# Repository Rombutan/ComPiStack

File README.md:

# YOU MUST SET A KICAD VARIABLE CALLED 'BASE_GIT_FOLDER' to the location of the root, git folder you cloned.

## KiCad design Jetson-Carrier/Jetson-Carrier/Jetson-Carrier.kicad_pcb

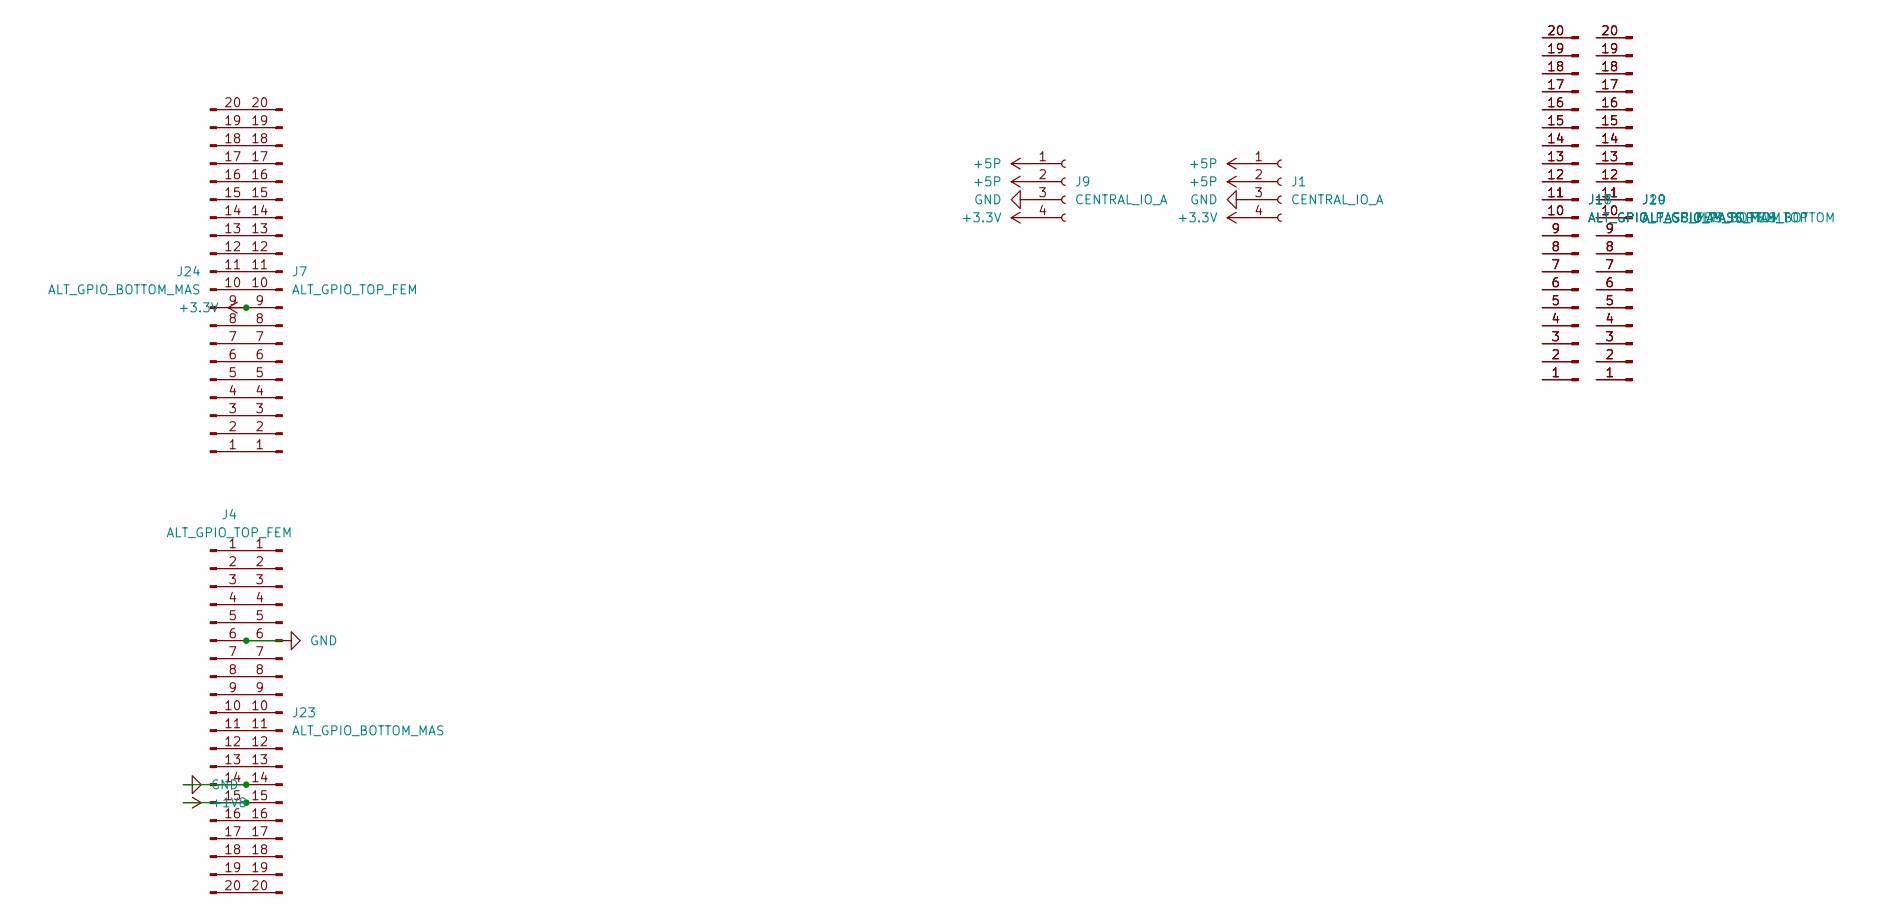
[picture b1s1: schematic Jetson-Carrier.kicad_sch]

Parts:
J1, J9: CENTRAL_IO_A; PinHeader_1x04_P2.54mm_Vertical
J4, J7: ALT_GPIO_TOP_FEM; 10132797-021100LF
J16, J20: ALT_GPIO_PASS_FEM_TOP; 10132797-021100LF
J17, J19: ALT_GPIO_PASS_MAS_BOTTOM; 10132798-022100LF
J23, J24: ALT_GPIO_BOTTOM_MAS; 10132798-022100LF

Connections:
+1V8: J4.15, J23.15
+3V3: J1.4, J7.9, J9.4, J24.9
+5P: J1.1, J1.2, J9.1, J9.2
GND: J1.3, J4.6, J4.14, J9.3, J23.6, J23.14
unnamed: J7.1, J24.1
unnamed: J7.2, J24.2
unnamed: J7.3, J24.3
unnamed: J16.1, J17.1
unnamed: J16.2, J17.2
unnamed: J16.3, J17.3
unnamed: J16.4, J17.4
unnamed: J16.5, J17.5
unnamed: J16.6, J17.6
unnamed: J16.7, J17.7
unnamed: J16.8, J17.8
unnamed: J16.9, J17.9
unnamed: J16.10, J17.10
unnamed: J16.11, J17.11
unnamed: J16.12, J17.12
unnamed: J16.13, J17.13
unnamed: J16.14, J17.14
unnamed: J16.15, J17.15
unnamed: J16.16, J17.16
unnamed: J16.17, J17.17
unnamed: J16.18, J17.18
unnamed: J16.19, J17.19
unnamed: J16.20, J17.20
unnamed: J19.1, J20.1
unnamed: J19.2, J20.2
unnamed: J19.3, J20.3
unnamed: J19.4, J20.4
unnamed: J19.5, J20.5
unnamed: J19.6, J20.6
unnamed: J19.7, J20.7
unnamed: J19.8, J20.8
unnamed: J19.9, J20.9
unnamed: J19.10, J20.10
unnamed: J19.11, J20.11
unnamed: J19.12, J20.12
unnamed: J19.13, J20.13
unnamed: J19.14, J20.14
unnamed: J19.15, J20.15
unnamed: J19.16, J20.16
unnamed: J19.17, J20.17
unnamed: J19.18, J20.18
unnamed: J19.19, J20.19
unnamed: J19.20, J20.20
unnamed: J4.1, J23.1
unnamed: J4.2, J23.2
unnamed: J4.3, J23.3
unnamed: J4.4, J23.4
unnamed: J4.5, J23.5
unnamed: J4.7, J23.7
unnamed: J4.8, J23.8
unnamed: J4.9, J23.9
unnamed: J4.10, J23.10
unnamed: J4.11, J23.11
unnamed: J4.12, J23.12
unnamed: J4.13, J23.13
unnamed: J4.16, J23.16
unnamed: J4.17, J23.17
unnamed: J4.18, J23.18
unnamed: J4.19, J23.19
unnamed: J4.20, J23.20
unnamed: J7.4, J24.4
unnamed: J7.5, J24.5
unnamed: J7.6, J24.6
unnamed: J7.7, J24.7
unnamed: J7.8, J24.8
unnamed: J7.10, J24.10
unnamed: J7.11, J24.11
unnamed: J7.12, J24.12
unnamed: J7.13, J24.13
unnamed: J7.14, J24.14
unnamed: J7.15, J24.15
unnamed: J7.16, J24.16
unnamed: J7.17, J24.17
unnamed: J7.18, J24.18
unnamed: J7.19, J24.19
unnamed: J7.20, J24.20

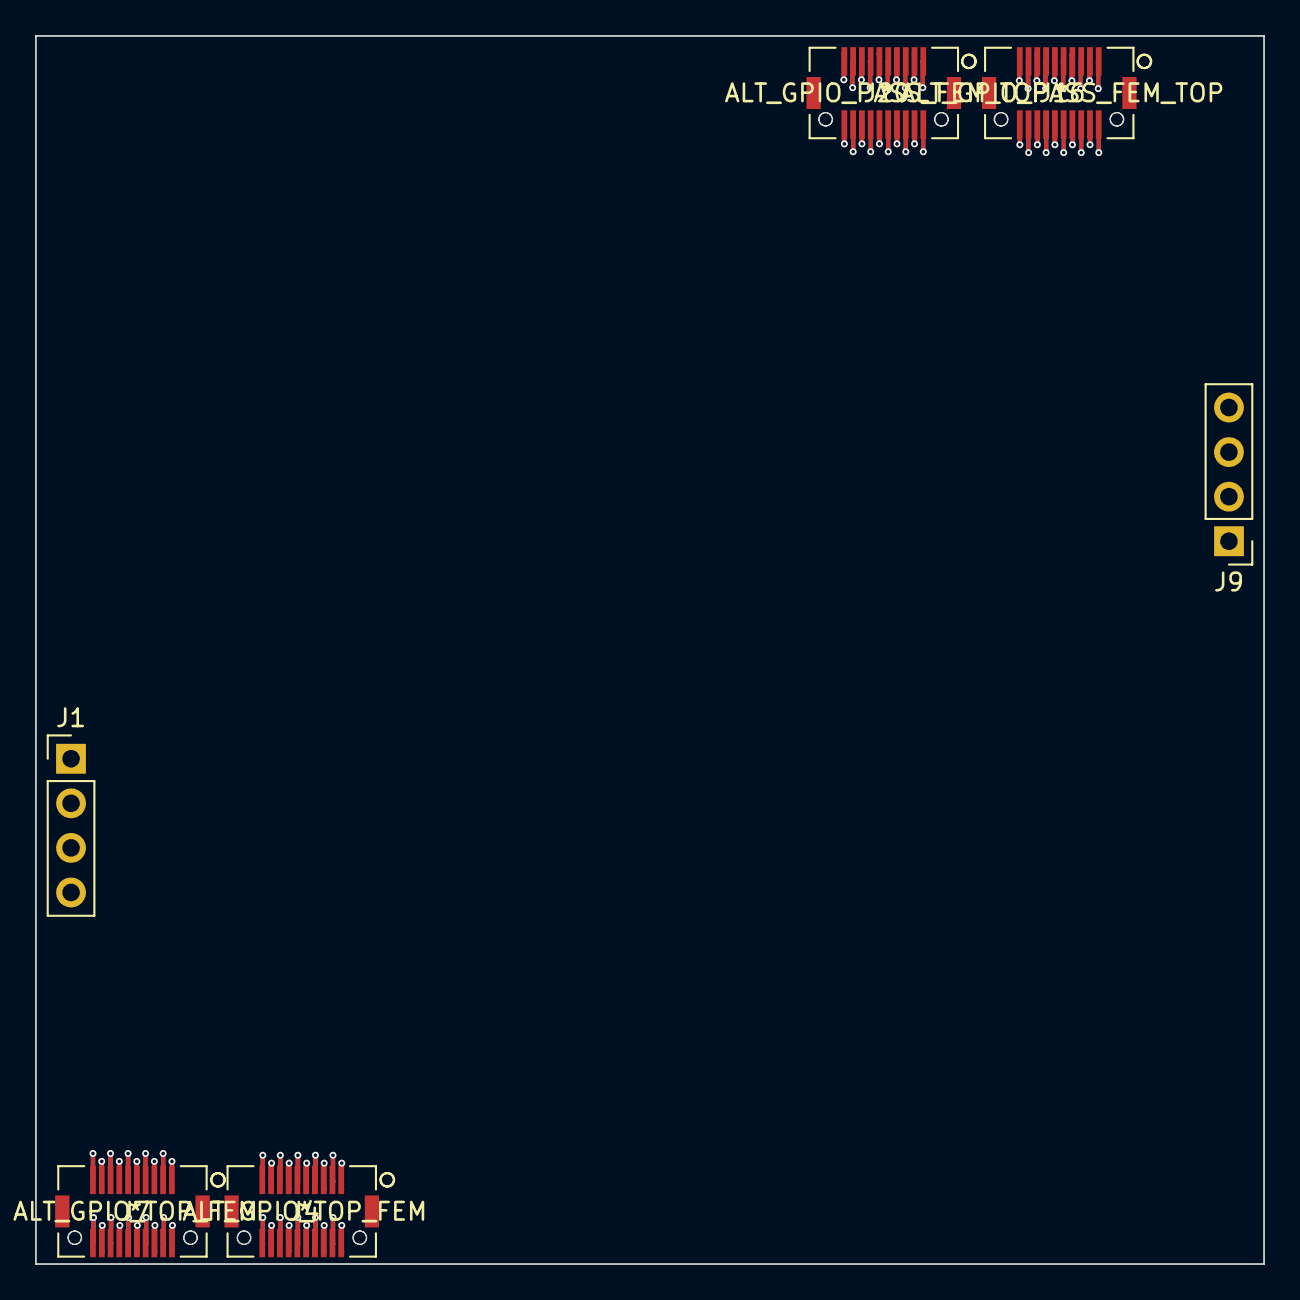
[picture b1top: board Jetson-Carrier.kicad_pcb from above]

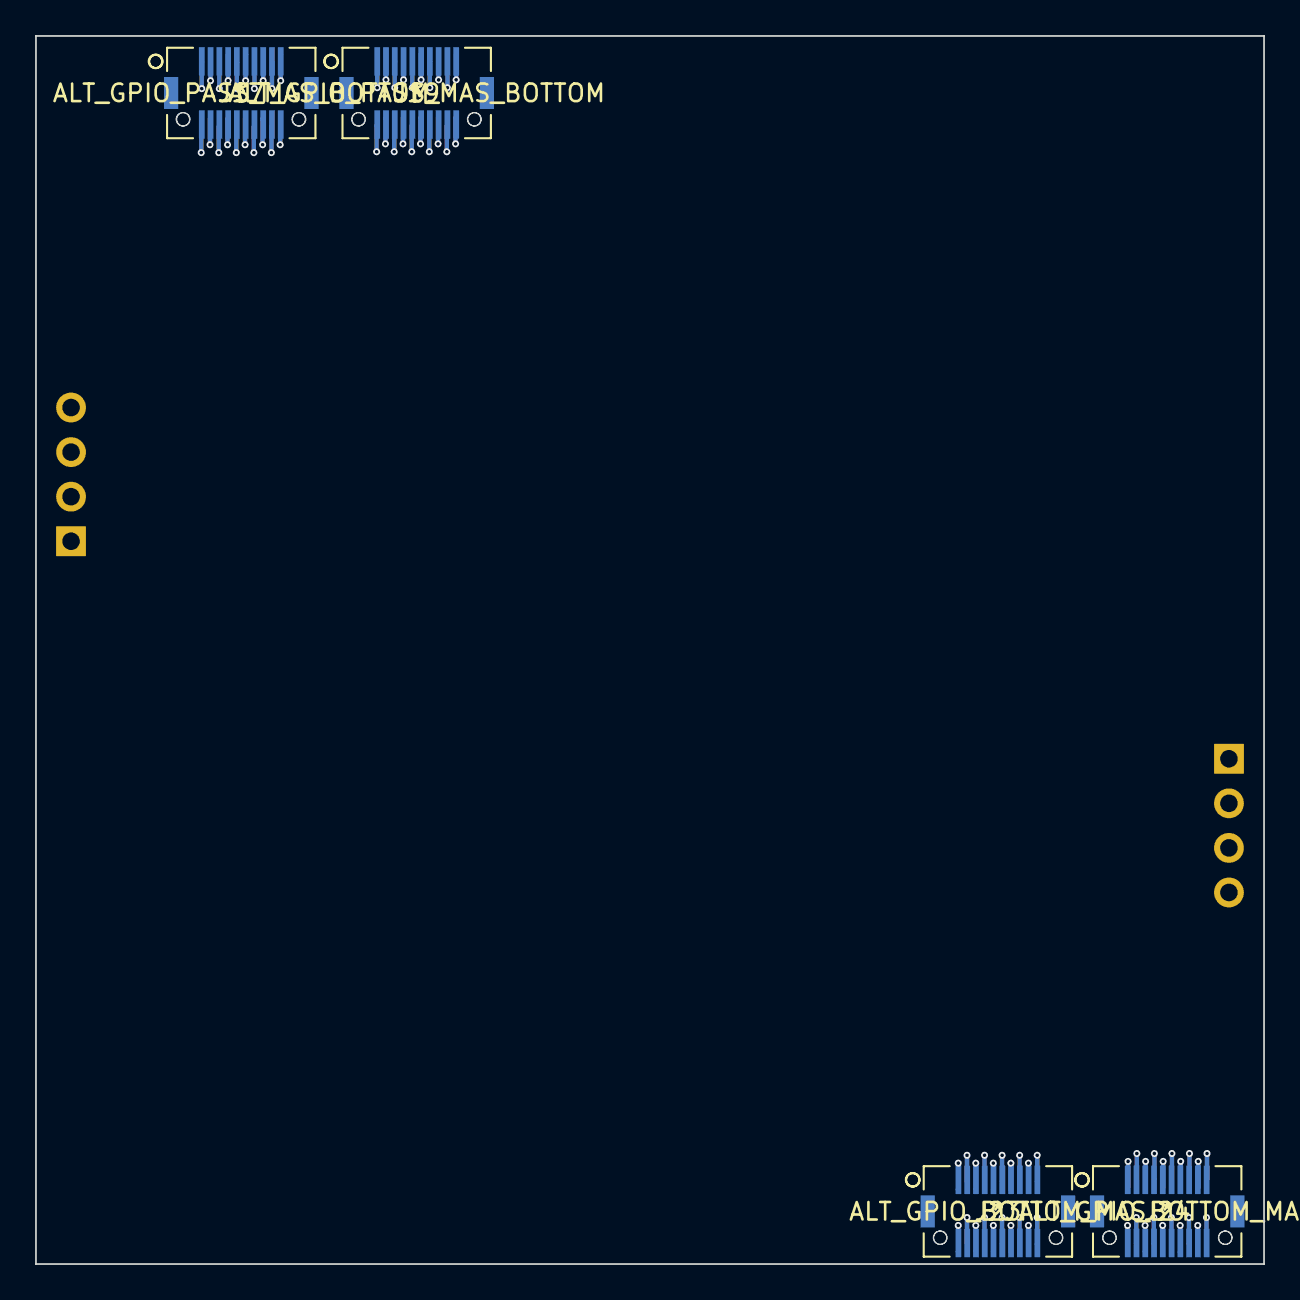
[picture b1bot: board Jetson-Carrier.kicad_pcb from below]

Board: 2 copper layers, 70.0 x 70.0 mm, 10 parts (4 on the bottom side), 80 nets.

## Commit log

2021-09-06 initial copy
2021-09-06 figure out how tf to do path vars

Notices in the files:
parts and their libraries:
Copyright 2021 Accelerated Designs. All rights reserved.
